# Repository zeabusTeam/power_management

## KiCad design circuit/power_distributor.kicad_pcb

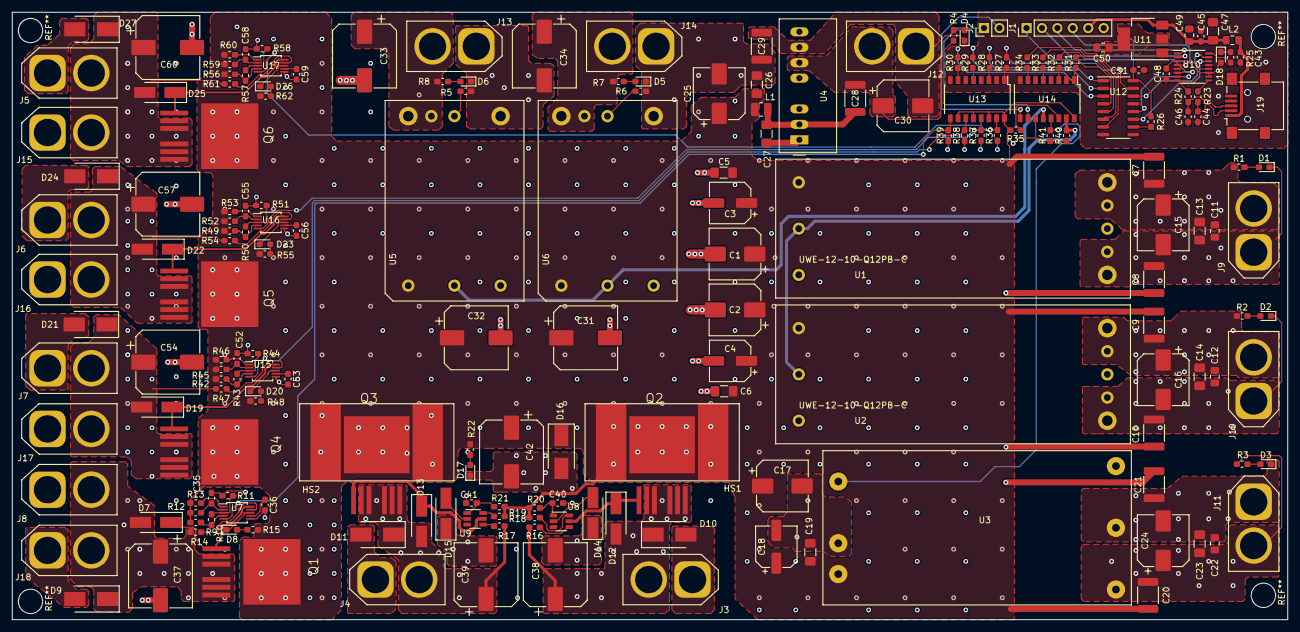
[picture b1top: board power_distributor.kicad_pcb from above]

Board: 4 copper layers, 210.0 x 100.0 mm, 195 parts (0 on the bottom side), 119 nets.

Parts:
C1, C2, C15, C16, C17, C24, C25, C30: 100uF; CP_Elec_8x10
C3, C4, C18: 22uF; CP_Elec_6.3x5.8
C5, C6, C13, C14, C19, C23, C26, C27: 10uF; C_1206_3216Metric_Pad1.42x1.75mm_HandSolder
C7, C8, C9, C10, C20, C21, C28, C29: 1000pF,3kV; C_1812_4532Metric_Pad1.30x3.40mm_HandSolder
C11, C12, C22, C49, C50: 1uF; C_0805_2012Metric_Pad1.15x1.40mm_HandSolder
C31, C32, C33, C34, C37, C38, C39, C42, C54, C57, C60: 220uF; CP_Elec_10x10
C35, C40, C41, C45, C48, C51, C52, C55, C58: 0.1uF; C_0603_1608Metric_Pad1.05x0.95mm_HandSolder
C36, C53, C56, C59: 150nF; C_0603_1608Metric_Pad1.05x0.95mm_HandSolder
C43: 0.01uF; C_0603_1608Metric_Pad1.05x0.95mm_HandSolder
C44, C46: 47pF; C_0603_1608Metric_Pad1.05x0.95mm_HandSolder
C47: 4.7uF; C_1206_3216Metric_Pad1.42x1.75mm_HandSolder
D1: 12V_On_1; LED_0603_1608Metric_Pad1.05x0.95mm_HandSolder
D2: 12V_On_2; LED_0603_1608Metric_Pad1.05x0.95mm_HandSolder
D3: 5V_On; LED_0603_1608Metric_Pad1.05x0.95mm_HandSolder
D4: 24V_On; LED_0603_1608Metric_Pad1.05x0.95mm_HandSolder
D5: 8.4V On_2; LED_0603_1608Metric_Pad1.05x0.95mm_HandSolder
D6: 8.4V On_1; LED_0603_1608Metric_Pad1.05x0.95mm_HandSolder
D7, D12, D13, D19, D22, D25: SMAJ17CA; D_SMA_Handsoldering
D8, D20, D23, D26: Thruster_ON; LED_0603_1608Metric_Pad1.05x0.95mm_HandSolder
D9, D10, D11, D16, D21, D24, D27: SMBJ26A; D_SMB_Handsoldering
D14, D15: SS16T3G; D_SMA_Handsoldering
D17: Main On; LED_0603_1608Metric_Pad1.05x0.95mm_HandSolder
D18: USB_On; LED_0603_1608Metric_Pad1.05x0.95mm_HandSolder
HS1, HS2: DA-T263-101E; HeatSink-DA-T263-101E
J1: UART; PinHeader_1x06_P2.54mm_Vertical
J2: Opto_AUX; PinHeader_1x02_P2.54mm_Vertical
J3, J4, J5, J6, J7, J8, J9, J10, J11, J12, J13, J14, J15, J16, J17, J18: AMASS XT60; AMASS_XT60-F_1x02_P7.20mm_Vertical
J19: USB_B_Mini; USB_Mini-B_Lumberg_2486_01_Horizontal
L1: 10uH,1A; L_1008_2520Metric
L2: Ferrite 600R 2A; L_0805_2012Metric_Pad1.15x1.40mm_HandSolder
Q1, Q4, Q5, Q6: AUIRFS8409-7P; D2PAK-7
Q2: IPB009N03LG; D2PAK-7
Q3: IPB009N03L_G; D2PAK-7
R1, R2: 3.6k; R_0603_1608Metric_Pad1.05x0.95mm_HandSolder
R3, R35: 1k; R_0603_1608Metric_Pad1.05x0.95mm_HandSolder
R4: 7.5k; R_0603_1608Metric_Pad1.05x0.95mm_HandSolder
R5, R6, R36, R37, R38, R39, R40, R41: 3.3k; R_0603_1608Metric_Pad1.05x0.95mm_HandSolder
R7, R8: 2.4k; R_0603_1608Metric_Pad1.05x0.95mm_HandSolder
R9, R14, R15, R26, R42, R47, R48, R49, R54, R55, R56, R61, R62: 10k; R_0603_1608Metric_Pad1.05x0.95mm_HandSolder
R10, R43, R50, R57: 160; R_0603_1608Metric_Pad1.05x0.95mm_HandSolder
R11, R44, R51, R58: 1.27k; R_0603_1608Metric_Pad1.05x0.95mm_HandSolder
R12, R20, R21, R45, R52, R59: 100; R_0603_1608Metric_Pad1.05x0.95mm_HandSolder
R13, R46, R53, R60: 8.66k; R_0603_1608Metric_Pad1.05x0.95mm_HandSolder
R16, R17, R18, R19: 0; R_0603_1608Metric_Pad1.05x0.95mm_HandSolder
R22: 5.6k; R_0603_1608Metric_Pad1.05x0.95mm_HandSolder
R23, R24: 27; R_0603_1608Metric_Pad1.05x0.95mm_HandSolder
R25: 270; R_0603_1608Metric_Pad1.05x0.95mm_HandSolder
R27, R28, R29, R30, R31, R32, R33: 200; R_0603_1608Metric_Pad1.05x0.95mm_HandSolder
R34: 220; R_0603_1608Metric_Pad1.05x0.95mm_HandSolder
U1, U2: UWE-12-10-Q12PB-C; UWE-xxxx
U3: UEI30-050-Q12P-C; UEI30
U4: TMR_6-2415WI; Converter_DCDC_TRACO_TMR-xxxx_THT
U5, U6: i6A4W020A033V-001-R; I6A
U7, U15, U16, U17: LM5060; MSOP-10_3x3mm_P0.5mm
U8, U9: LM5050-1; TSOT-23-6
U10: FT230XS; SSOP-16_3.9x4.9mm_P0.635mm
U11: LM1117-3.3; SOT-223-3_TabPin2
U12: 74AHC595D; SOIC-16_3.9x9.9mm_P1.27mm
U13, U14: PS2801C-4; SOP-16_4.4x10.4mm_P1.27mm

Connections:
/Battery_ORing/+BATT: C1.1, C2.1, C3.1, C4.1, C5.1, C6.1, C7.2, C9.2, C17.1, C18.1, C19.1, C20.2, C25.1, C26.1, C31.1, C32.1, C42.1, D16.1, HS1.1, HS2.1, L1.1, Q1.D, Q2.D, Q3.D, Q4.D, Q5.D, Q6.D, R9.1, R12.1, R13.1, R15.1, R18.1, R19.1, R20.1, R21.1, R22.1, R35.2, R42.1, R45.1, R46.1, R48.1, R49.1, R52.1, R53.1, R55.1, R56.1, R59.1, R60.1, R62.1, U1.1, U2.1, U3.1, U5.1, U6.1, U13.10, U13.12, U13.14, U13.16, U14.16
/Battery_ORing/+BATT_1: C38.1, D10.1, D12.2, J3.2, Q2.S, R16.1
/Battery_ORing/+BATT_2: C39.1, D11.1, D13.2, J4.2, Q3.S, R17.1
/DC/DC_conveters/+5V_ISOLATED: C20.1, C22.1, C23.1, C24.1, J11.2, R3.1, U3.4
/DC/DC_conveters/+8.4V_1: C33.1, J13.2, R8.1, U5.7, U5.8
/DC/DC_conveters/+8.4V_2: C34.1, J14.2, R7.1, U6.7, U6.8
/DC/DC_conveters/+12V_ISOLATED_1: C7.1, C11.1, C13.1, C15.1, J9.2, R1.1, U1.7, U1.8
/DC/DC_conveters/+12V_ISOLATED_2: C9.1, C12.1, C14.1, C16.1, J10.2, R2.1, U2.7, U2.8
/DC/DC_conveters/+24V_ISOLATED: C28.1, C30.1, J12.2, R4.1, U4.6
/DC/DC_conveters/EN_5V: R41.2, U3.3, U14.13
/DC/DC_conveters/EN_8.4V: U5.2, U6.2, U14.12
/DC/DC_conveters/EN_12V: R40.2, U1.2, U2.2, U14.15
/DC/DC_conveters/GND_5V_ISOLATED: C21.1, C22.2, C23.2, C24.2, D3.1, J11.1, U3.5
/DC/DC_conveters/GND_12V_ISOLATED_1: C8.1, C11.2, C13.2, C15.2, D1.1, J9.1, U1.4, U1.5
/DC/DC_conveters/GND_12V_ISOLATED_2: C10.1, C12.2, C14.2, C16.2, D2.1, J10.1, U2.4, U2.5
/DC/DC_conveters/GND_24V_ISOLATED: C29.1, C30.2, D4.1, J12.1, U4.7
/Thruster_Switch_1/+Vout: C60.1, D25.2, D27.1, J5.2, J15.2, Q6.S, R61.1
/Thruster_Switch_1/EN: R36.2, U13.15, U17.5
/Thruster_Switch_2/+Vout: C57.1, D22.2, D24.1, J6.2, J16.2, Q5.S, R54.1
/Thruster_Switch_2/EN: R37.2, U13.13, U16.5
/Thruster_Switch_3/+Vout: C54.1, D19.2, D21.1, J7.2, J17.2, Q4.S, R47.1
/Thruster_Switch_3/EN: R38.2, U13.11, U15.5
/Thruster_Switch_4/+Vout: C37.1, D7.2, D9.1, J8.2, J18.2, Q1.S, R14.1
/Thruster_Switch_4/EN: R39.2, U7.5, U13.9
/USB_Interface/D+: C46.1, J19.3, R24.2
/USB_Interface/D-: C44.1, J19.2, R23.2
/USB_Interface/D_M: R23.1, U10.9
/USB_Interface/D_P: R24.1, U10.8
/USB_Interface/OPTO_C: J2.1, U14.10
/USB_Interface/OPTO_E: J2.2, U14.9
/USB_Interface/RXD: J1.4, U10.4
/USB_Interface/TXD: J1.3, U10.1
/USB_Interface/VCCIO: C48.1, D18.2, U10.3, U10.10, U10.11
/USB_Interface/~CTS: J1.1, U10.6
/USB_Interface/~RTS: J1.2, U10.2
GND: C43.2, C44.2, C45.2, C46.2, C47.2, C48.2, C49.2, C50.2, C51.2, J1.6, J19.4, J19.5, J19.6, U10.5, U10.13, U11.1, U12.8, U12.13, U13.2, U13.4, U13.6, U13.8, U14.2, U14.4, U14.6, U14.8
GNDPWR: C1.2, C2.2, C3.2, C4.2, C5.2, C6.2, C8.2, C10.2, C17.2, C18.2, C19.2, C21.2, C25.2, C26.2, C27.2, C29.2, C31.2, C32.2, C33.2, C34.2, C35.2, C36.2, C37.2, C38.2, C39.2, C40.2, C41.2, C42.2, C52.2, C53.2, C54.2, C55.2, C56.2, C57.2, C58.2, C59.2, C60.2, D5.1, D6.1, D9.2, D10.2, D11.2, D14.1, D15.1, D16.2, D17.1, D21.2, D24.2, D27.2, J3.1, J4.1, J5.1, J6.1, J7.1, J8.1, J13.1, J14.1, J15.1, J16.1, J17.1, J18.1, R5.1, R6.1, R11.2, R36.1, R37.1, R38.1, R39.1, R40.1, R41.1, R44.2, R51.2, R58.2, U1.3, U2.3, U3.2, U4.1, U5.3, U5.4, U6.3, U6.4, U7.6, U14.11, U15.6, U16.6, U17.6
unnamed: C27.1, C28.2, L1.2, U4.2
unnamed: C35.1, R12.2, U7.2
unnamed: C36.1, U7.7
unnamed: C40.1, R20.2, U8.1
unnamed: C41.1, R21.2, U9.1
unnamed: C43.1, J19.1, L2.1
unnamed: C50.1, C51.1, R26.2, U11.2, U12.16
unnamed: C52.1, R45.2, U15.2
unnamed: C53.1, U15.7
unnamed: C55.1, R52.2, U16.2
unnamed: C56.1, U16.7
unnamed: C58.1, R59.2, U17.2
unnamed: C59.1, U17.7
unnamed: D1.2, R1.2
unnamed: D2.2, R2.2
unnamed: D3.2, R3.2
unnamed: D4.2, R4.2
unnamed: D5.2, R7.2
unnamed: D6.2, R8.2
unnamed: D7.1, Q1.G, U7.10
unnamed: D8.1, U7.8
unnamed: D8.2, R15.2
unnamed: D12.1, Q2.G, U8.5
unnamed: D13.1, Q3.G, U9.5
unnamed: D14.2, U8.2
unnamed: D15.2, U9.2
unnamed: D17.2, R22.2
unnamed: D18.1, R25.2
unnamed: D19.1, Q4.G, U15.10
unnamed: D20.1, U15.8
unnamed: D20.2, R48.2
unnamed: D22.1, Q5.G, U16.10
unnamed: D23.1, U16.8
unnamed: D23.2, R55.2
unnamed: D25.1, Q6.G, U17.10
unnamed: D26.1, U17.8
unnamed: D26.2, R62.2
unnamed: R5.2, U5.6
unnamed: R6.2, U6.6
unnamed: R9.2, R10.1, U7.4
unnamed: R10.2, R11.1, U7.3
unnamed: R13.2, U7.1
unnamed: R14.2, U7.9
unnamed: R16.2, U8.4
unnamed: R17.2, U9.4
unnamed: R18.2, U8.6
unnamed: R19.2, U9.6
unnamed: R25.1, U10.16
unnamed: R26.1, U12.10
unnamed: R27.1, U13.1
unnamed: R27.2, U12.15
unnamed: R28.1, U13.3
unnamed: R28.2, U12.1
unnamed: R29.1, U13.5
unnamed: R29.2, U12.2
unnamed: R30.1, U13.7
unnamed: R30.2, U12.3
unnamed: R31.1, U14.1
unnamed: R31.2, U12.4
unnamed: R32.1, U14.3
unnamed: R32.2, U12.5
unnamed: R33.1, U14.5
unnamed: R33.2, U12.6
unnamed: R34.1, U14.7
unnamed: R34.2, U12.7
unnamed: R35.1, U14.14
unnamed: R42.2, R43.1, U15.4
unnamed: R43.2, R44.1, U15.3
unnamed: R46.2, U15.1
unnamed: R47.2, U15.9
unnamed: R49.2, R50.1, U16.4
unnamed: R50.2, R51.1, U16.3
unnamed: R53.2, U16.1
unnamed: R54.2, U16.9
unnamed: R56.2, R57.1, U17.4
unnamed: R57.2, R58.1, U17.3
unnamed: R60.2, U17.1
unnamed: R61.2, U17.9
unnamed: U10.7, U12.12
unnamed: U10.14, U12.11
unnamed: U10.15, U12.14
VBUS: C45.1, C47.1, C49.1, J1.5, L2.2, U10.12, U11.3

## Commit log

2020-03-28 (Real) Initial commit
    This is the initial commit fter gathering file from Dome
2020-03-29 Finish schematic. Ready for footprint assignment
    Finish the first version of schematic.
2020-03-30 Finsh annotation and footprint assignment
2020-03-31 Remove redundant protection. Finish lay-out. Also, generated BOM
2020-04-04 Place all electrical planes and plane vias
2020-04-07 Complete all PCB routing.
2020-04-20 Add VBUS output to RS232 connector
2020-04-21 Change LDO to LM1117-3.3
2022-07-21 Update to Kicad6
